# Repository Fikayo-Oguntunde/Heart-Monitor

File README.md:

# Heart-Monitor
Monitor for heart beat.

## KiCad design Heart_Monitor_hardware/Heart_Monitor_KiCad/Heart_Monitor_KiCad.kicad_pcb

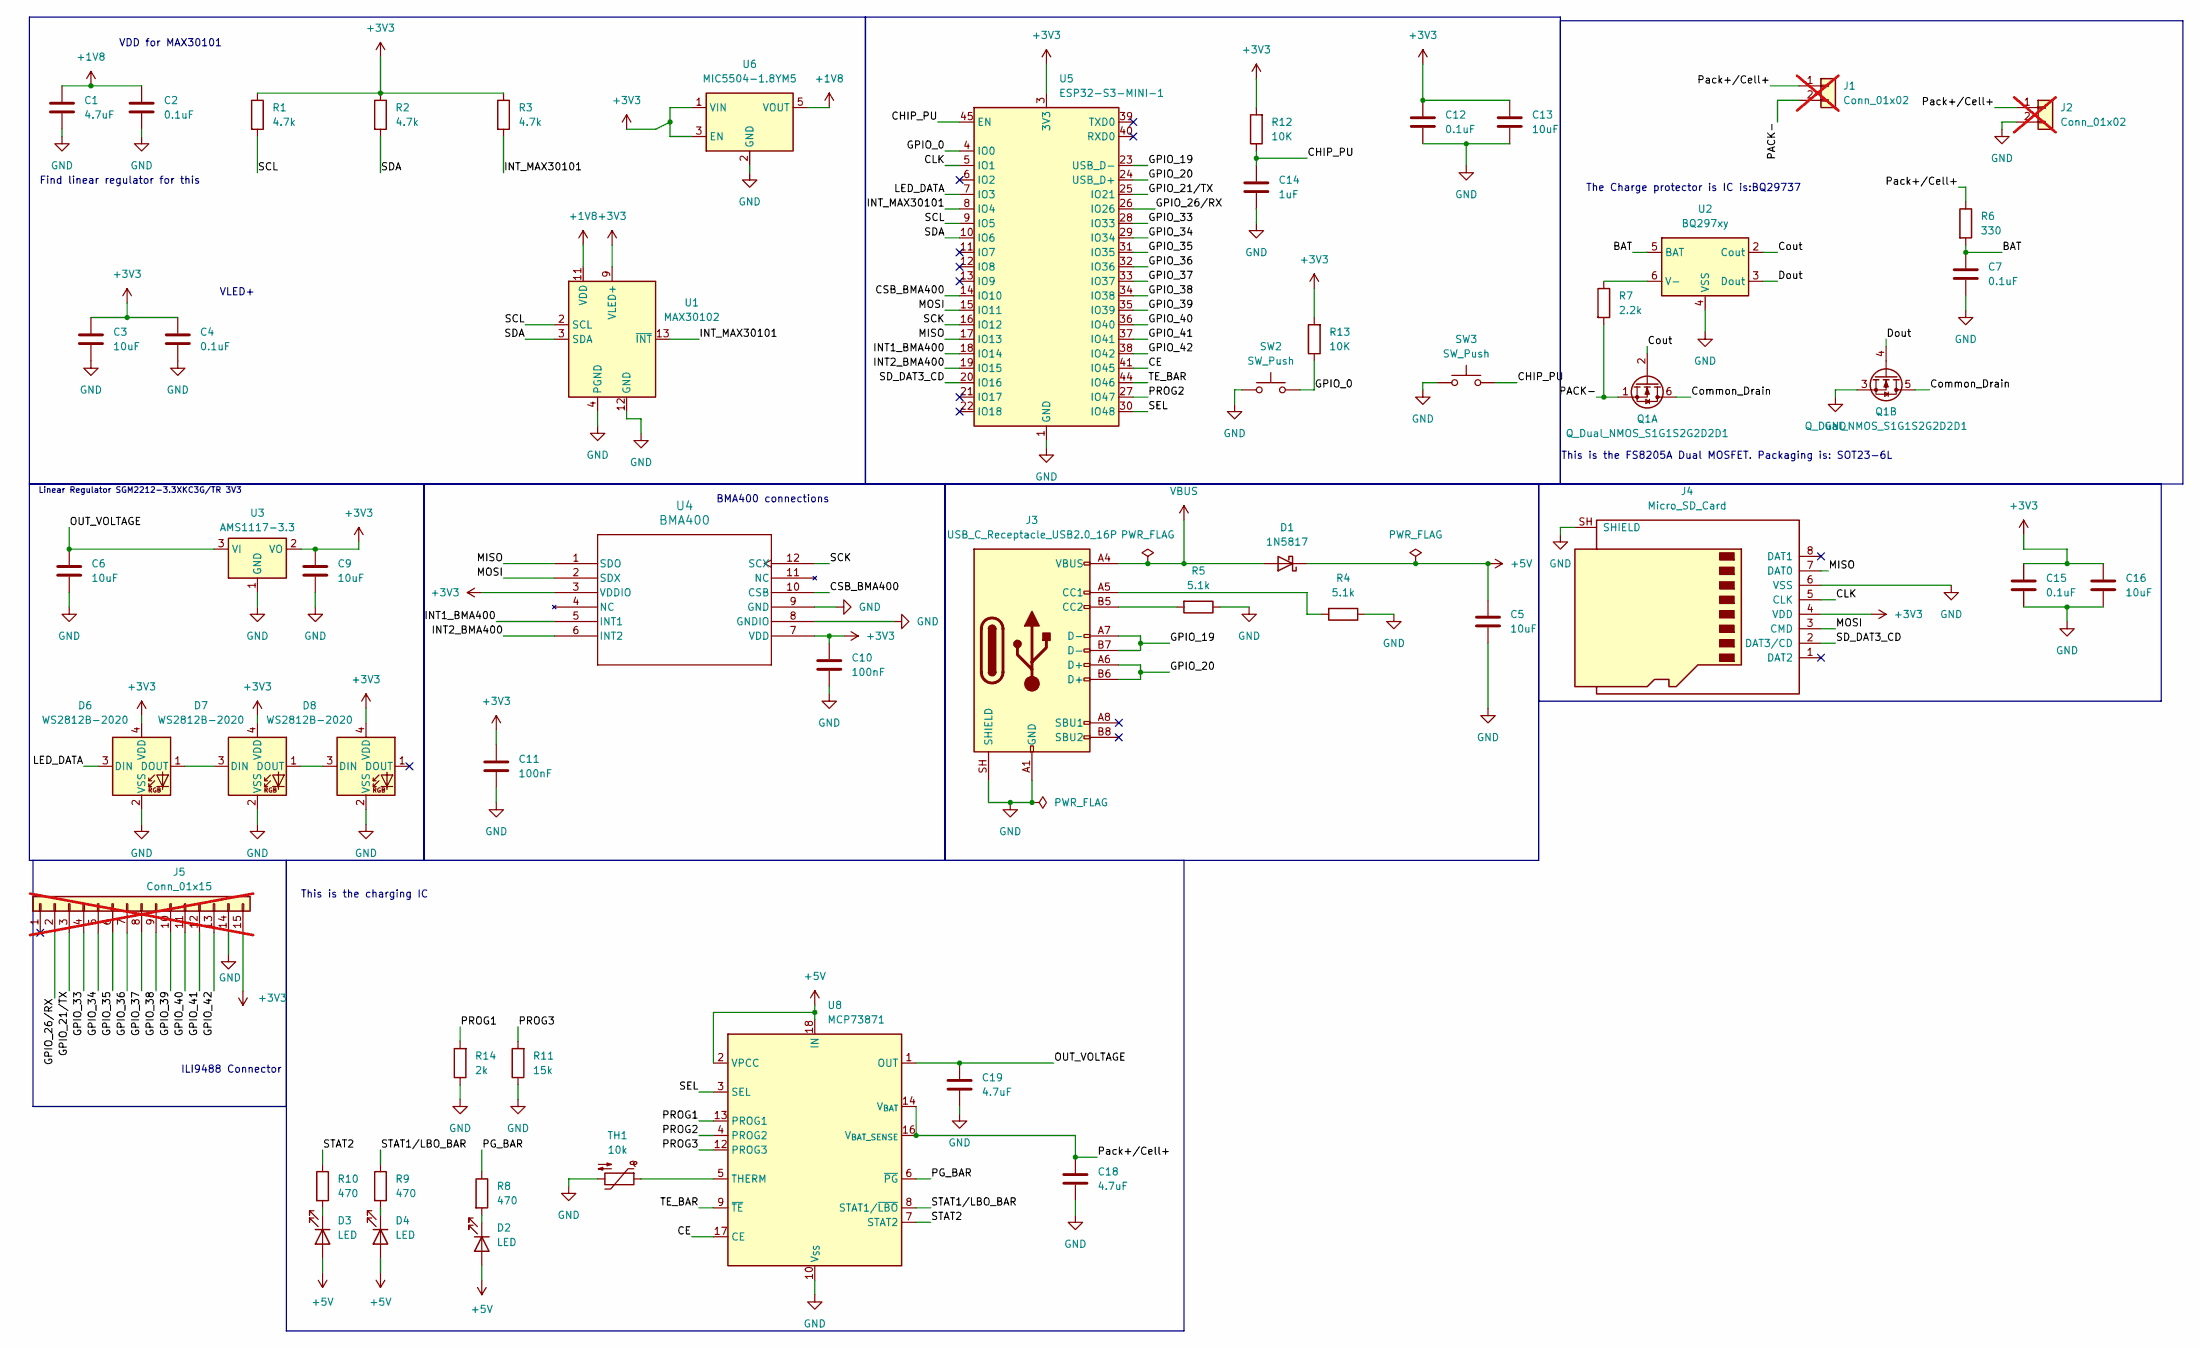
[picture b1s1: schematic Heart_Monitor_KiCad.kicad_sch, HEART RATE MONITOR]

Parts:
C1, C18, C19: 4.7uF; C_0603_1608Metric
C2, C4, C7, C12, C15: 0.1uF; C_0603_1608Metric
C3, C5, C6, C9, C13, C16: 10uF; C_0603_1608Metric
C10, C11: 100nF; C_0603_1608Metric
C14: 1uF; C_0603_1608Metric
D1: 1N5817; D_SOD-123
D2, D3, D4: LED; LED_0603_1608Metric
D6, D7, D8: WS2812B-2020; LED_WS2812B-2020_PLCC4_2.0x2.0mm
J1, J2: Conn_01x02; SolderWire-0.5sqmm_1x02_P4.6mm_D0.9mm_OD2.1mm_Relief; not fitted
J3: USB_C_Receptacle_USB2.0_16P; USB_C_Receptacle_HRO_TYPE-C-31-M-12
J4: Micro_SD_Card; microSD_HC_Molex_47219-2001
J5: Conn_01x15; PinHeader_1x15_P2.54mm_Horizontal; not fitted
Q1: Q_Dual_NMOS_S1G1S2G2D2D1; TSOT-23-6_HandSoldering
R1, R2, R3: 4.7k; R_0805_2012Metric
R4, R5: 5.1k; R_0805_2012Metric
R6: 330; R_0805_2012Metric
R7: 2.2k; R_0805_2012Metric
R8, R9, R10: 470; R_0805_2012Metric
R11: 15k; R_0805_2012Metric
R12, R13: 10K; R_0805_2012Metric
R14: 2k; R_0805_2012Metric
SW2, SW3: SW_Push; SW_SPST_EVQP0
TH1: 10k; R_0603_1608Metric
U1: MAX30102; Maxim_OLGA-14_3.3x5.6mm_P0.8mm
U2: BQ297xy; WSON-6_1.5x1.5mm_P0.5mm
U3: AMS1117-3.3; SOT-223-3_TabPin2
U4: BMA400; LGA-12_2x2mm_P0.5mm
U5: ESP32-S3-MINI-1
U6: MIC5504-1.8YM5; SOT-23-5
U8: MCP73871; QFN-20-1EP_4x4mm_P0.5mm_EP2.5x2.5mm

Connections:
+1V8: C1.1, C2.1, U1.11 (VDD), U6.5 (VOUT)
+3V3: C3.1, C4.1, C9.1, C10.1, C11.1, C12.1, C13.1, C15.1, C16.1, D6.4 (VDD), D7.4 (VDD), D8.4 (VDD), J4.4 (VDD), J5.15, R1.1, R2.1, R3.1, R12.2, R13.2, U1.9 (VLED+), U1.10 (VLED+), U3.2 (VO), U4.3 (VDDIO), U4.7 (VDD), U5.3 (3V3), U6.1 (VIN), U6.3 (EN)
+5V: C5.1, D1.1 (K), D2.2 (A), D3.2 (A), D4.2 (A), U8.2 (VPCC), U8.18 (IN), U8.19 (IN)
/BAT: C7.1, R6.2, U2.5 (BAT)
/CE: U5.41 (IO45), U8.17 (CE)
/CHIP_PU: C14.1, R12.1, SW3.2, U5.45 (EN)
/CLK: J4.5 (CLK), U5.5 (IO1)
/CSB_BMA400: U4.10 (CSB), U5.14 (IO10)
/Common_Drain: Q1.5 (D), Q1.6 (D)
/Cout: Q1.2 (G), U2.2 (Cout)
/Dout: Q1.4 (G), U2.3 (Dout)
/GPIO_0: R13.1, SW2.2, U5.4 (IO0)
/GPIO_19: J3.A7 (D-), J3.B7 (D-), U5.23 (USB_D-)
/GPIO_20: J3.A6 (D+), J3.B6 (D+), U5.24 (USB_D+)
/GPIO_21/TX: J5.3, U5.25 (IO21)
/GPIO_26/RX: J5.2, U5.26 (IO26)
/GPIO_33: J5.4, U5.28 (IO33)
/GPIO_34: J5.5, U5.29 (IO34)
/GPIO_35: J5.6, U5.31 (IO35)
/GPIO_36: J5.7, U5.32 (IO36)
/GPIO_37: J5.8, U5.33 (IO37)
/GPIO_38: J5.9, U5.34 (IO38)
/GPIO_39: J5.10, U5.35 (IO39)
/GPIO_40: J5.11, U5.36 (IO40)
/GPIO_41: J5.12, U5.37 (IO41)
/GPIO_42: J5.13, U5.38 (IO42)
/INT1_BMA400: U4.5 (INT1), U5.18 (IO14)
/INT2_BMA400: U4.6 (INT2), U5.19 (IO15)
/INT_MAX30101: R3.2, U1.13 (~INT), U5.8 (IO4)
/LED_DATA: D6.3 (DIN), U5.7 (IO3)
/MISO: J4.7 (DAT0), U4.1 (SDO), U5.17 (IO13)
/MOSI: J4.3 (CMD), U4.2 (SDX), U5.15 (IO11)
/OUT_VOLTAGE: C6.1, C19.1, U3.3 (VI), U8.1 (OUT), U8.20 (OUT)
/PACK-: J1.2, Q1.1 (S), R7.2
/PG_BAR: R8.1, U8.6 (~PG)
/PROG1: R14.2, U8.13 (PROG1)
/PROG2: U5.27 (IO47), U8.4 (PROG2)
/PROG3: R11.2, U8.12 (PROG3)
/Pack+/Cell+: C18.1, J1.1, J2.1, R6.1, U8.14 (V_{BAT}), U8.15 (V_{BAT}), U8.16 (V_{BAT_SENSE})
/SCK: U4.12 (SCX), U5.16 (IO12)
/SCL: R1.2, U1.2 (SCL), U5.9 (IO5)
/SDA: R2.2, U1.3 (SDA), U5.10 (IO6)
/SD_DAT3_CD: J4.2 (DAT3/CD), U5.20 (IO16)
/SEL: U5.30 (IO48), U8.3 (SEL)
/STAT1/LBO_BAR: R9.1, U8.8 (STAT1/~LBO)
/STAT2: R10.1, U8.7 (STAT2)
/TE_BAR: U5.44 (IO46), U8.9 (~TE)
GND: C1.2, C2.2, C3.2, C4.2, C5.2, C6.2, C7.2, C9.2, C10.2, C11.2, C12.2, C13.2, C14.2, C15.2, C16.2, C18.2, C19.2, D6.2 (VSS), D7.2 (VSS), D8.2 (VSS), J2.2, J3.A1 (GND), J3.A12 (GND), J3.B1 (GND), J3.B12 (GND), J3.SH (SHIELD), J4.6 (VSS), J4.SH (SHIELD), J5.14, Q1.3 (S), R4.1, R5.1, R11.1, R14.1, SW2.1, SW3.1, TH1.2, U1.4 (PGND), U1.12 (GND), U2.4 (VSS), U3.1 (GND), U4.8 (GNDIO), U4.9 (GND), U5.1 (GND), U5.2 (GND), U5.42 (GND), U5.43 (GND), U5.46 (GND), U5.47 (GND), U5.48 (GND), U5.49 (GND), U5.50 (GND), U5.51 (GND), U5.52 (GND), U5.53 (GND), U5.54 (GND), U5.55 (GND), U5.56 (GND), U5.57 (GND), U5.58 (GND), U5.59 (GND), U5.60 (GND), U5.61 (GND), U5.62 (GND), U5.63 (GND), U5.64 (GND), U5.65 (GND), U6.2 (GND), U8.10 (V_{SS}), U8.11 (V_{SS}), U8.21 (V_{SS})
unnamed: D2.1 (K), R8.2
unnamed: D3.1 (K), R10.2
unnamed: D4.1 (K), R9.2
unnamed: D6.1 (DOUT), D7.3 (DIN)
unnamed: D7.1 (DOUT), D8.3 (DIN)
unnamed: J3.A5 (CC1), R4.2
unnamed: J3.B5 (CC2), R5.2
unnamed: R7.1, U2.6 (V-)
unnamed: TH1.1, U8.5 (THERM)
VBUS: D1.2 (A), J3.A4 (VBUS), J3.A9 (VBUS), J3.B4 (VBUS), J3.B9 (VBUS)

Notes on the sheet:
Find linear regulator for this
VLED+
VDD for MAX30101
BMA400 connections
The Charge protector is IC is:BQ29737
Linear Regulator SGM2212-3.3XKC3G/TR 3V3
This is the charging IC
ILI9488 Connector
This is the FS8205A Dual MOSFET. Packaging is: SOT23-6L

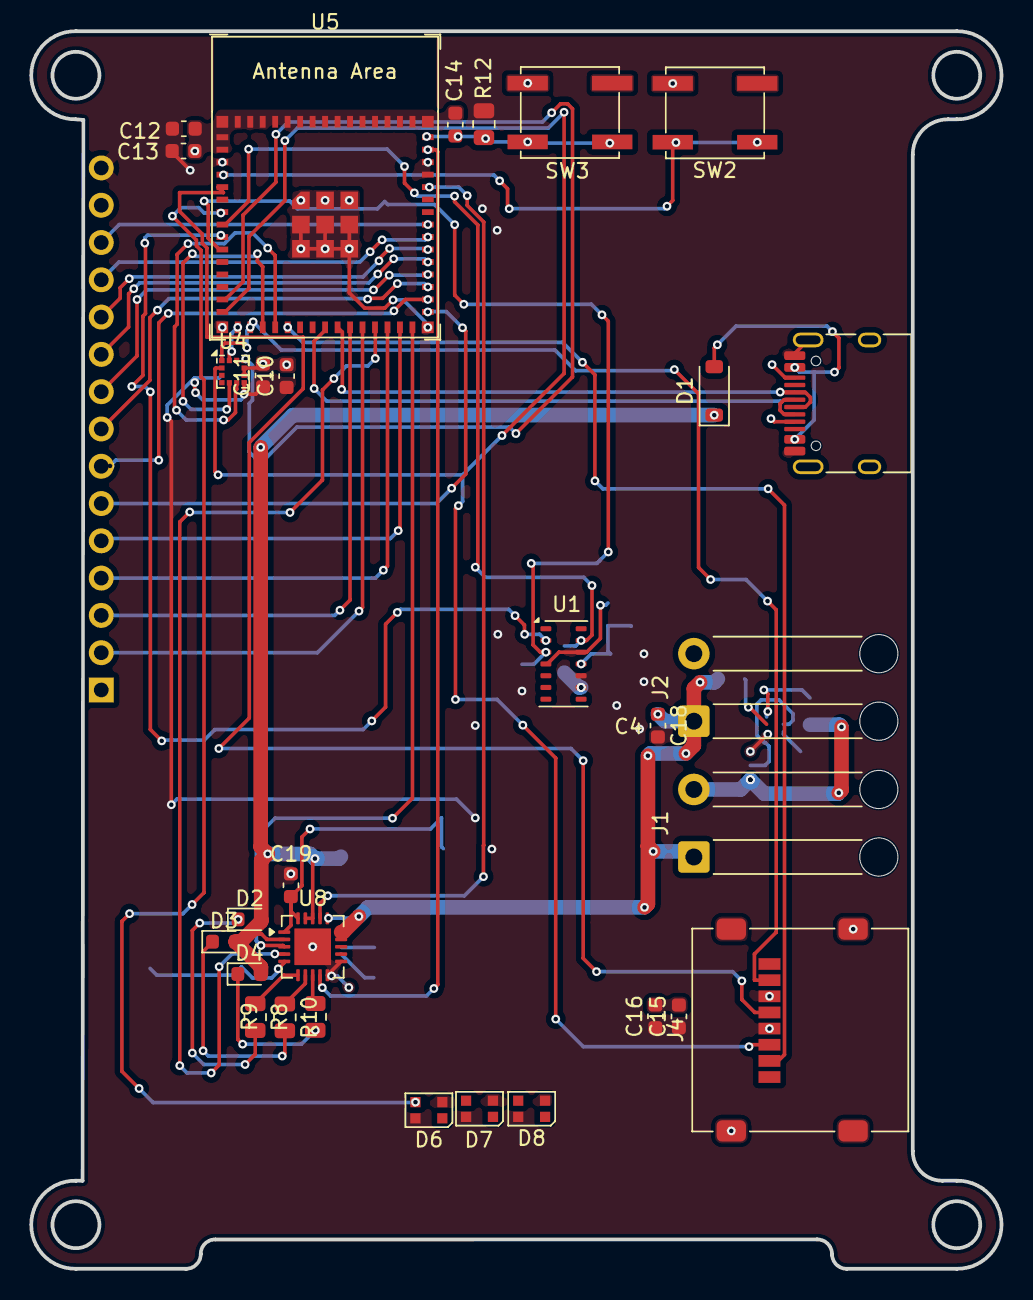
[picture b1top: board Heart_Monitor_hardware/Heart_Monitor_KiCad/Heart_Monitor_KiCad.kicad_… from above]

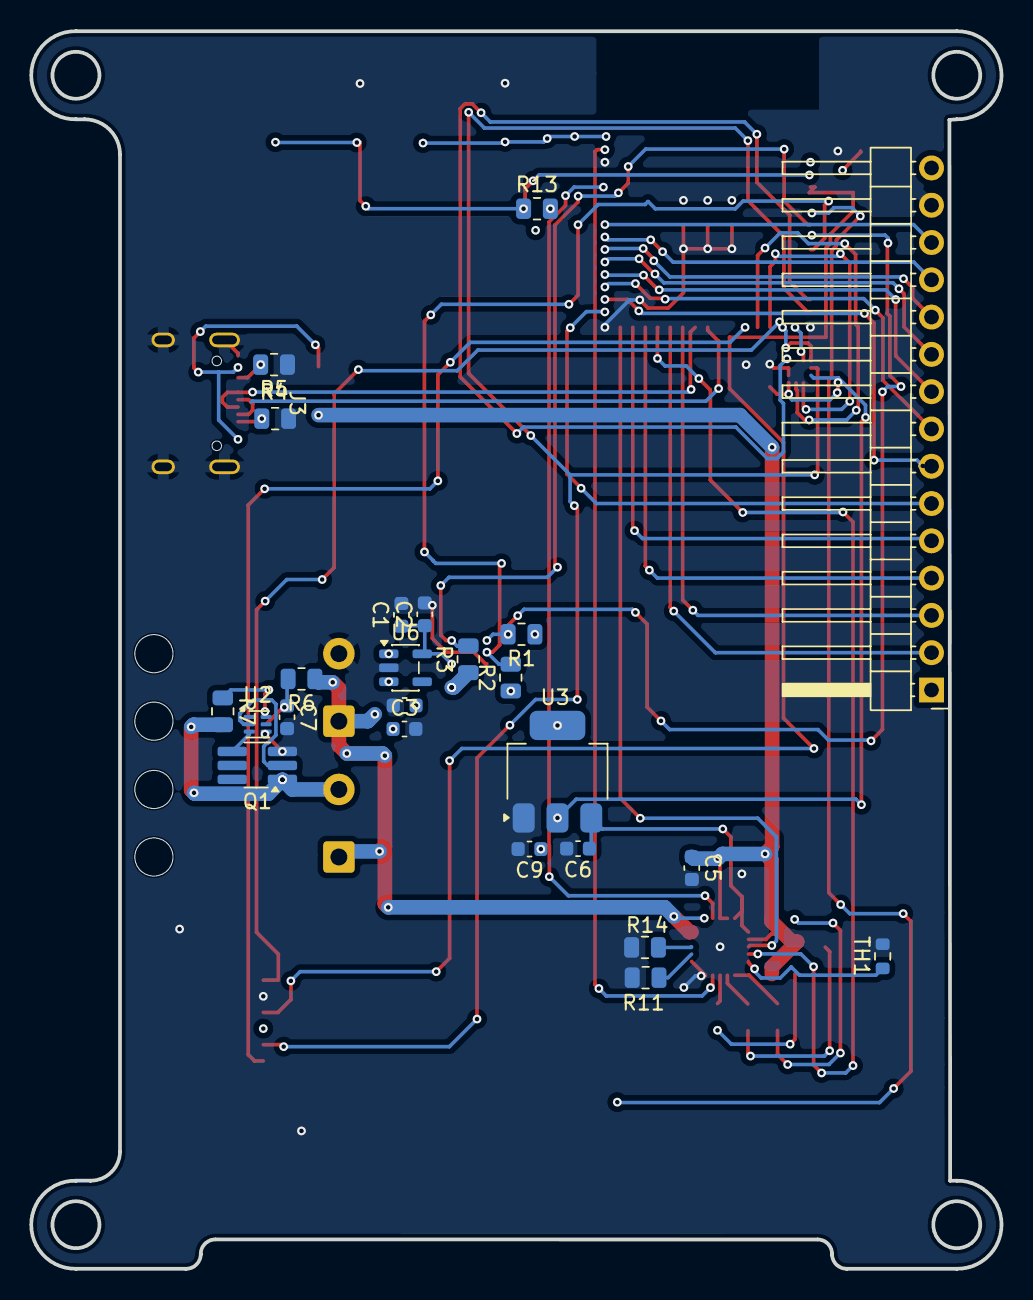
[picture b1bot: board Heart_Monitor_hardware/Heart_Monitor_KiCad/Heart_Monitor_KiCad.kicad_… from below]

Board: 2 copper layers, 66.1 x 84.3 mm, 54 parts (24 on the bottom side), 58 nets.

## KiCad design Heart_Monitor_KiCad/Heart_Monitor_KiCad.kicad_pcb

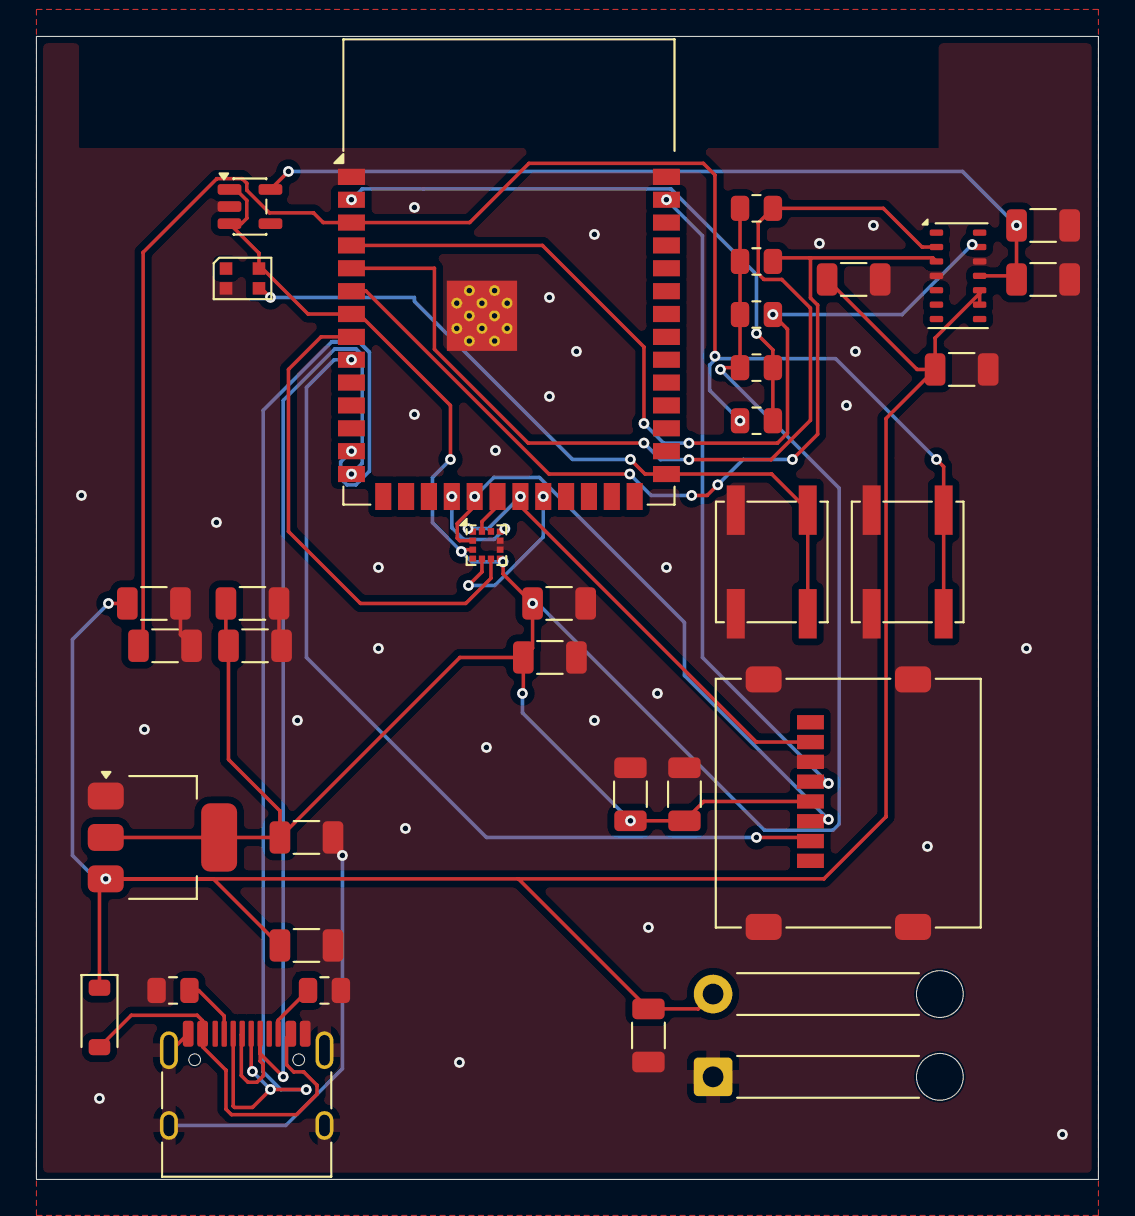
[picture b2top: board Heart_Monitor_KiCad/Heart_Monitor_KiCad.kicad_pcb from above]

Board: 2 copper layers, 59.0 x 63.5 mm, 34 parts (0 on the bottom side), 23 nets.

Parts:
C1: 4.7uF; C_1206_3216Metric
C2, C4, C12, C15: 0.1uF; C_1206_3216Metric
C3, C5, C6, C9, C13, C16, C17: 10uF; C_1206_3216Metric
C10, C11: 100nF; C_1206_3216Metric
C14: 1uF; C_1206_3216Metric
D1: 1N5817; D_SOD-123
D6: WS2812B-2020; LED_WS2812B-2020_PLCC4_2.0x2.0mm
J2: Conn_01x02; SolderWire-0.5sqmm_1x02_P4.6mm_D0.9mm_OD2.1mm_Relief
J3: USB_C_Receptacle_USB2.0_16P; USB_C_Receptacle_HRO_TYPE-C-31-M-12
J4: Micro_SD_Card; microSD_HC_Molex_47219-2001
R1, R2, R3: 4.7k; R_0805_2012Metric
R4, R5: 5.1k; R_0805_2012Metric
R11: 0; R_0805_2012Metric
R12: 10K; R_0805_2012Metric
SW2, SW3: SW_Push; SW_SPST_EVQP0
U1: MAX30102; Maxim_OLGA-14_3.3x5.6mm_P0.8mm
U2: ESP32-S3-WROOM-1
U3: AMS1117-3.3; SOT-223-3_TabPin2
U4: BMA400; LGA-12_2x2mm_P0.5mm
U6: MIC5504-1.8YM5; SOT-23-5

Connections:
+1V8: C1.1, C2.1, U1.11 (VDD), U6.5 (VOUT)
+5V: C3.1, C4.1, C5.1, C6.1, C17.1, D1.1 (K), J2.2, U1.9 (VLED+), U1.10 (VLED+), U3.3 (VI)
/CHIP_PU: C14.1, R12.1, SW3.2, U2.3 (EN)
/CLK: J4.5 (CLK), U2.39 (IO1)
/CSB_BMA400: U2.18 (IO10), U4.10 (CSB)
/ESP_3V3: R11.2, R12.2, U2.2 (3V3)
/GPIO0: D6.3 (DIN), SW2.2, U2.27 (IO0)
/GPIO19: J3.A7 (D-), J3.B7 (D-), U2.13 (USB_D-)
/GPIO20: J3.A6 (D+), J3.B6 (D+), U2.14 (USB_D+)
/INT1_BMA400: U2.22 (IO14), U4.5 (INT1)
/INT2_BMA400: U2.8 (IO15), U4.6 (INT2)
/INT_MAX30101_conn: R3.2, U1.13 (~INT), U2.4 (IO4)
/MISO: J4.7 (DAT0), U2.21 (IO13), U4.1 (SDO)
/MOSI: J4.3 (CMD), U2.19 (IO11), U4.2 (SDX)
/SCK: U2.20 (IO12), U4.12 (SCX)
/SCL_MAX30101_conn: R1.2, U1.2 (SCL), U2.5 (IO5)
/SDA_MAX30101_conn: R2.2, U1.3 (SDA), U2.6 (IO6)
/SD_DAT3_CD: J4.2 (DAT3/CD), U2.9 (IO16)
/SD_VDD: C9.1, C10.1, C11.1, C12.1, C13.1, C15.1, C16.1, D6.4 (VDD), J4.4 (VDD), R1.1, R2.1, R3.1, R11.1, U2.7 (IO7), U3.2 (VO), U4.3 (VDDIO), U4.7 (VDD), U6.1 (VIN), U6.3 (EN)
/VBUS: D1.2 (A), J3.A4 (VBUS), J3.A9 (VBUS), J3.B4 (VBUS), J3.B9 (VBUS)
GND: C1.2, C2.2, C3.2, C4.2, C5.2, C6.2, C9.2, C10.2, C11.2, C12.2, C13.2, C14.2, C15.2, C16.2, C17.2, D6.2 (VSS), J2.1, J3.A1 (GND), J3.A12 (GND), J3.B1 (GND), J3.B12 (GND), J3.SH (SHIELD), J4.6 (VSS), J4.SH (SHIELD), R4.1, R5.1, SW2.1, SW3.1, U1.4 (PGND), U1.12 (GND), U2.1 (GND), U2.40 (GND), U2.41 (GND), U3.1 (GND), U4.8 (GNDIO), U4.9 (GND), U6.2 (GND)
unnamed: J3.A5 (CC1), R4.2
unnamed: J3.B5 (CC2), R5.2
